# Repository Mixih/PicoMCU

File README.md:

# PicoMCU

General purpose MCU breakout boards. Pico series boards are extra small or low
power and optimized for low profile embedding, and Micro series board are
general purpose development and prototyping boards with rich peripherals for testing.

## Contents

- PicoMEGA 328PB: Tiny (24x25mm) ATMEGA328PB breakout board

## File Layout

- `Lib`: shared component and footprint libraries
- `[Board Name]/`
  - `[Board Name].pro`: Main KiCAD project file
  - `[Board Name]_panelized.pro`: PCB layout panelized to fill 100x100mm fab
    area 

## Detailed Description and Specifications

Here are the details for each of the hardware projects hosted here.

### PicoMEGA 328PB

This is intended to be a general, low power ATMEGA328PB breakout board, sized as
to be small enough to be embedded in other products (i.e. hardware mods). By
keeping the MCU in sleep mode, power consumption can be greatly reduced,
making the 328PB a viable option for battery powered electronics.

**Feature:**
- Ultra-low quiescent (Iq = 400nA typ) current 3V3 switching regulator (300mA max) 
  w/ regulator bypass jumper for higher power.
- External crystal (designed for 8Mhz max system clock) with compensation caps
- AVCC supply filtering per Atmel AN042 (omit by jumpering over)
- Reset ESD protection and debounce/ext pullup
- ISCP header
- All hardware pins broken out (no more microwire to pad prototyping)
- Optional indication LED connected to pin E1 for status indication needs
  (leave unpopulated if using TWI1 or low power)

**Intentional Omissions:**
- PWR/UART Status LED: Waste of quiescent power. Kludge in if needed.
- Reset button: takes too much space. Use jumper wire instead if manual reset
  is needed

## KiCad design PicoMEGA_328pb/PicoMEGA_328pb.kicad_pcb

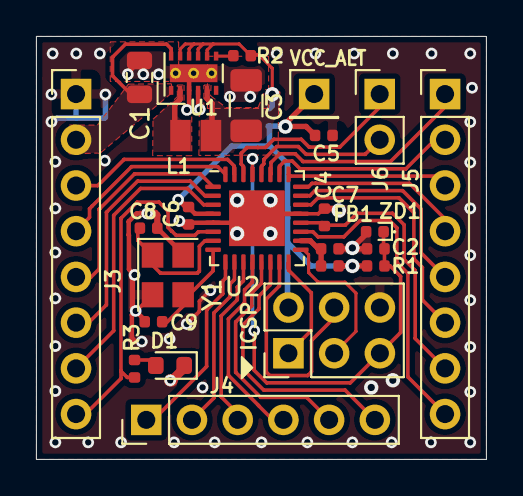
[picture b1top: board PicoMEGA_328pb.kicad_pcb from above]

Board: 2 copper layers, 25.0 x 23.5 mm, 26 parts (1 on the bottom side), 36 nets.

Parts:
C1: 10u; C_0805_2012Metric
C2, C4, C6, C7: 0.1u; C_0402_1005Metric
C3: 22u; C_1206_3216Metric
C5: 1u; C_0402_1005Metric
C8, C9: 16p; C_0402_1005Metric
D1: LED; LED_0603_1608Metric
FB1: 220@100Mhz; L_0402_1005Metric
J1: ICSP; PinHeader_2x03_P2.54mm_Vertical
J2: 3V3; PinHeader_1x01_P2.54mm_Vertical
J3: GPIO BLK A; PinHeader_1x08_P2.54mm_Vertical
J4: GPIO BLK B; PinHeader_1x06_P2.54mm_Vertical
J5: GPIO BLK C; PinHeader_1x08_P2.54mm_Vertical
J6: GPIO BLK D; PinHeader_1x02_P2.54mm_Vertical
JP1: VREG_ENA; MicroJumper-2_P0.3mm_Open_Pad0.75x1mm
L1: 4.7u; L_0806_2016metric
R1: 15k; R_0402_1005Metric
R2: 100k; R_0402_1005Metric
R3: 500; R_0402_1005Metric
U1: TPS62745DSSR; WSON-12-1EP_3x2mm_P0.5mm_EP1x2.65_ThermalVias
U2: ATmega328PB-MU; QFN-32-1EP_5x5mm_P0.5mm_EP3.1x3.1mm
Y1: 8Mhz; Crystal_SMD_3225-4Pin_3.2x2.5mm
ZD1: D6V3H1U2LP; D_0402_1005Metric

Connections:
+3V3: C5.1, C6.1, FB1.1, J1.2, J2.1, JP1.2, R1.1, U2.4
+9V: C1.1, J3.2, U1.1, U1.12
/3V3_REG: C3.1, JP1.1, L1.2, R2.1, U1.5, U1.8, U1.9, U1.10, U1.11
/AREF: C4.1, J5.7, U2.20
/MISO: J1.1, U2.16
/MOSI: J1.4, U2.15
/PB0: J4.4, U2.12
/PB1: J4.5, U2.13
/PB2: J4.6, U2.14
/PC0: J5.5, U2.23
/PC1: J5.4, U2.24
/PC2: J5.3, U2.25
/PC3: J5.2, U2.26
/PC4: J5.1, U2.27
/PC5: J6.2, U2.28
/PD0: J6.1, U2.30
/PD1: J3.3, U2.31
/PD2: J3.4, U2.32
/PD3: J3.5, U2.1
/PD4: J3.6, U2.2
/PD5: J4.1, U2.9
/PD6: J4.2, U2.10
/PD7: J4.3, U2.11
/PE0: J3.7, U2.3
/PE1: J3.8, R3.2, U2.6
/PE2: J5.8, U2.19
/PE3: J5.6, U2.22
/PG: R2.2, U1.7
/RST: C2.1, J1.5, R1.2, U2.29, ZD1.1
/SCK: J1.3, U2.17
GND: C1.2, C2.2, C3.2, C4.2, C5.2, C6.2, C7.2, C8.1, C9.2, D1.1, J1.6, J3.1, U1.3, U1.4, U1.13, U2.5, U2.21, U2.33, Y1.2, Y1.4, ZD1.2
unnamed: C7.1, FB1.2, U2.18
unnamed: C8.2, U2.7, Y1.1
unnamed: C9.1, U2.8, Y1.3
unnamed: D1.2, R3.1
unnamed: L1.1, U1.2

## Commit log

2020-05-30 Root commit
2020-05-30 Git: Setup repo
    Added basic ignores and EoL norming.
2020-05-30 PicoMEGA 328PB: Add h/w design files
    Added initial (r0.1c) PicoMEGA ATmega328PB breakout forlow profile
    prototyping applications.
2020-05-30 PicoMEGA 328PB: rev0.1d
    Fixed V_in regulator to use input voltage for enable to gurantee the
    regulator powers on when an input voltage is applied.
2020-05-31 PicoMEGA 328PB: rev0.1e
    Revised clock area to use guard ring to prevent cross-talk interference
    for adjacent GPIO traces. No such protection of the GPIOs themselves
    though.
